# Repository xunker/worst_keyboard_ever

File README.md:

# Worst. Keyboard. Ever.

https://github.com/xunker/worst_keyboard_ever

It's a mechanical keyboard made from limit switches[^1]. Sorry.

## Parts

Part                      | Quantity | Notes
--------------------------|----------|------
[PCB](kicad)              | 1        | Using more than one is not recommended
Omron D2F-FL              | 66       | [^2]
1N4148 Diode              | 66       | SOT-123 package recommended, but you can use LL34 (MiniMELF) if you like things that roll away while you're soldering them
2.54MM pin (male) headers | 23 pos   | Use whatever fits in the holes[^3]
0805 LED                  | 3        | Prefer the kind that light up; LEDs that don't light up are not good indicators
0805 330 ohm resistor     | 3        | You'll learn to solder SMD components and you'll _like it_

Your microcontroller is not listed. Use whatever you like. There's [QMK firmware](#firmware) for the Pi Pico if you want it.

## Matrix

| row/col | 0    | 1   | 2   | 3    | 4    | 5    | 6    | 7   | 8   | 9   | 10  | 11   | 12   | 13    |
|---------|------|-----|-----|------|------|------|------|-----|-----|-----|-----|------|------|-------|
| 0       | esc  | 1   | 2   | 3    | 4    | 5    | 6    | 7   | 8   | 9   | 0   | -    | =    | bksp  |
| 1       | tab  | q   | w   | e    | r    | t    | y    | u   | i   | o   | p   | [    | ]    | \     |
| 2       | cap  | a   | s   | d    | f    | g    | h    | j   | k   | l   | ;   | '    | ent  | ---   |
| 3       | shft | z   | x   | c    | v    | b    | n    | m   | ,   | .   | /   | shft | up   | fn    |
| 4       | ctrl | win | alt |  --- | spc1 | spc2 | spc3 | --- | --- | alt | app | left | down | right |

## LEDs

The caps/num/scroll LEDs are _active-low_. That means the `common` pin should be connected to your microcontroller's VCC, and the LEDs are activated by pulling the approriate pin to ground.

If you're using a 3.3V MCU like the Pi Pico, do **NOT** connect `common` to a 5V source like VBUS or USB power. If you do that, you'll _fry_ your MCU you'll be sad.

## Firmware

There is QMK firmware available, targeting the Raspberry Pi Pico (RP2040). Find it in the [qmk_firmware](qmk_firmware/keyboards/wke_66) directory.

If you don't want to build it yourself, and you don't need to customize anything, a [prebuild .u2f file](./wke_wke_66_default.uf2) is also available.

# Useless Questions

## Why?

Because I needed **one** switch, but it was cheaper to buy a whole gross of them.

## The switches are too close together

I recommend installing smaller fingers on one or both hands.

## I've used worse keyboards than this!

1) "Worst. Keyboard. Ever." is a product/marketing name.
2) No you haven't.

## A Scroll Lock LED? Really?

Don't worry about it. No one in the history of the world has **ever** used Scroll Lock. No, not even _that one guy from the internet_, he's lying.

## Is there an ISO version?

Assuming drills exist, yes.

## It has no legends!

If you're asking for key legends, that means you want to use this as an _actual_ keyboard to type _real_ things. That's a crazy idea, you should stand up and slowly back away.

But, if you insist, [here are some suggestions](SERIOUSLY.md#no-legends).

## Your soldering is terrible!

Wrong, _MY_ soldering is AWESOME. My _cat's_ soldering is terrible.

Note: Cat hair seen in the [photos](images/) is __not included__.

# License

[CC BY-NC-SA 4.0](LICENSE)

[^1]: Variously called "limit switches", "lever switches", or "detect switches".

[^2]: Be honest, you're not going to use _real_ Omron switches, are you? You're going to use some knock-off, admit it.

[^3]: That's what she said.

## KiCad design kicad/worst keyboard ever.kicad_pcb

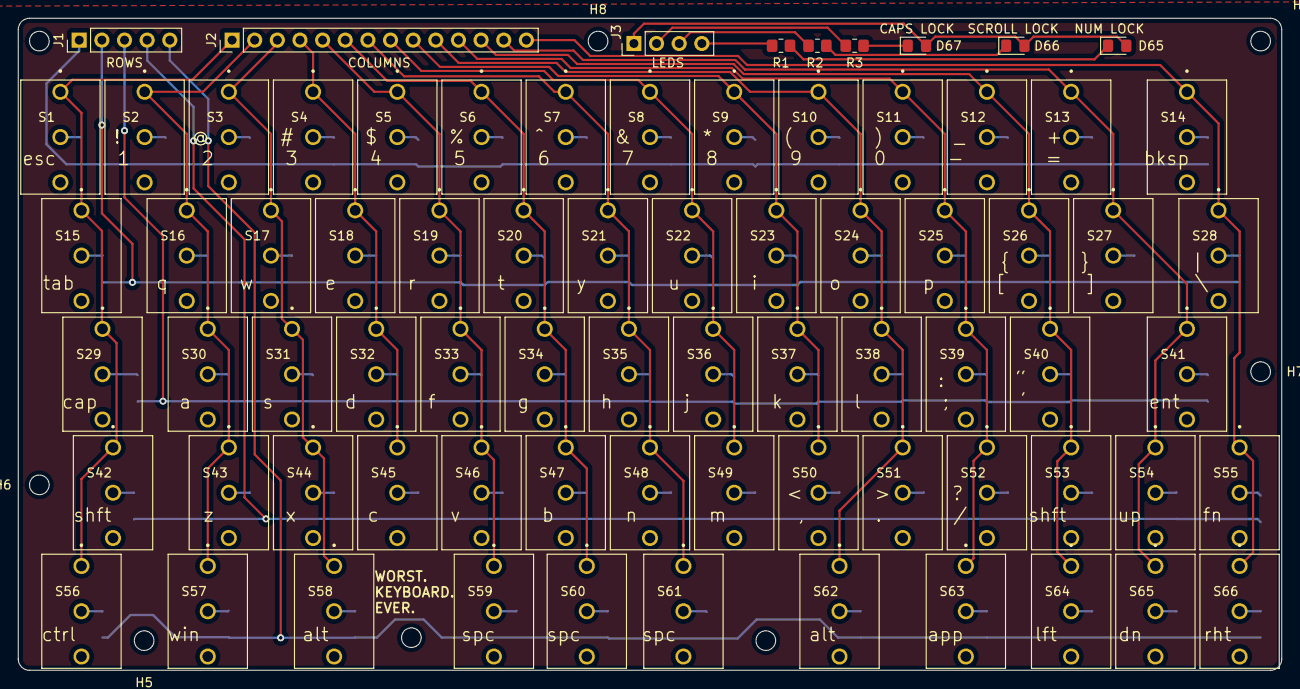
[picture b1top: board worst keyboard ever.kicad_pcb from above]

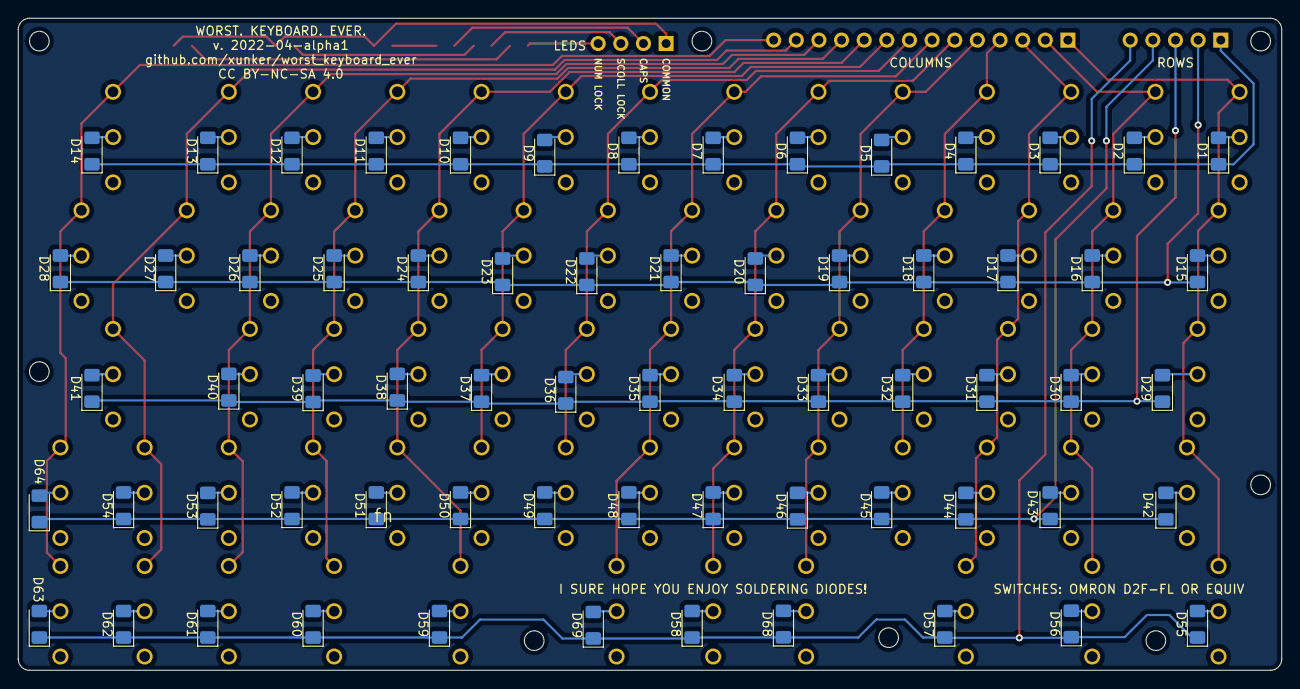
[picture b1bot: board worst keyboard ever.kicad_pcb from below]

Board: 2 copper layers, 141.8 x 73.1 mm, 149 parts (66 on the bottom side), 92 nets.

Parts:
D1, D2, D3, D4, D5, D6, D7, D8, D9, D10, D11, D12, D13, D14, D15, D16, D17, D18, D19, D20, D21, D22, D23, D24, D25, D26, D27, D28, D29, D30, D31, D32, D33, D34, D35, D36, D37, D38, D39, D40, D41, D42, D43, D44, D45, D46, D47, D48, D49, D50, D51, D52, D53, D54, D55, D56, D57, D58, D59, D60, D61, D62, D63, D64, D68, D69: D; D_1206_3216Metric_Pad1.42x1.75mm_HandSolder
D65, D66, D67: LED; LED_0805_2012Metric_Pad1.15x1.40mm_HandSolder
H1, H2, H3, H4, H5, H6, H7, H8: MountingHole; MountingHole_2.2mm_M2_DIN965
J1: Conn_01x05_Male; PinHeader_1x05_P2.54mm_Vertical
J2: Conn_01x14_Male; PinHeader_1x14_P2.54mm_Vertical
J3: Conn_01x04_Male; PinHeader_1x04_P2.54mm_Vertical
R1, R2, R3: R; R_0805_2012Metric_Pad1.20x1.40mm_HandSolder
S1, S2, S3, S4, S5, S6, S7, S8, S9, S10, S11, S12, S13, S14, S15, S16, S17, S18, S19, S20, S21, S22, S23, S24, S25, S26, S27, S28, S29, S30, S31, S32, S33, S34, S35, S36, S37, S38, S39, S40, S41, S42, S43, S44, S45, S46, S47, S48, S49, S50, S51, S52, S53, S54, S55, S56, S57, S58, S59, S60, S61, S62, S63, S64, S65, S66: D2F-FL; SW_D2F-FL_rotated_1.5xwide

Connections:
/CAPS_LOCK_LED: J3.2, R3.2
/LED_COMMON: D65.2 (A), D66.2 (A), D67.2 (A), J3.1
/NUM_LOCK_LED: J3.4, R1.2
/Row1: D1.1 (K), D2.1 (K), D3.1 (K), D4.1 (K), D5.1 (K), D6.1 (K), D7.1 (K), D8.1 (K), D9.1 (K), D10.1 (K), D11.1 (K), D12.1 (K), D13.1 (K), D14.1 (K), J1.1
/Row2: D15.1 (K), D16.1 (K), D17.1 (K), D18.1 (K), D19.1 (K), D20.1 (K), D21.1 (K), D22.1 (K), D23.1 (K), D24.1 (K), D25.1 (K), D26.1 (K), D27.1 (K), D28.1 (K), J1.2
/Row3: D29.1 (K), D30.1 (K), D31.1 (K), D32.1 (K), D33.1 (K), D34.1 (K), D35.1 (K), D36.1 (K), D37.1 (K), D38.1 (K), D39.1 (K), D40.1 (K), D41.1 (K), J1.3
/Row4: D42.1 (K), D43.1 (K), D44.1 (K), D45.1 (K), D46.1 (K), D47.1 (K), D48.1 (K), D49.1 (K), D50.1 (K), D51.1 (K), D52.1 (K), D53.1 (K), D54.1 (K), D64.1 (K), J1.4
/Row5: D55.1 (K), D56.1 (K), D57.1 (K), D58.1 (K), D59.1 (K), D60.1 (K), D61.1 (K), D62.1 (K), D63.1 (K), D68.1 (K), D69.1 (K), J1.5
/SCROLL_LOCK_LED: J3.3, R2.2
Col1: J2.1, S1.COM, S15.COM, S29.COM, S42.COM, S56.COM
Col2: J2.2, S2.COM, S16.COM, S30.COM, S43.COM, S57.COM
Col3: J2.3, S3.COM, S17.COM, S31.COM, S44.COM, S58.COM
Col4: J2.4, S4.COM, S18.COM, S32.COM, S45.COM
Col5: J2.5, S5.COM, S19.COM, S33.COM, S46.COM, S59.COM
Col6: J2.6, S6.COM, S20.COM, S34.COM, S47.COM, S60.COM
Col7: J2.7, S7.COM, S21.COM, S35.COM, S48.COM, S61.COM
Col8: J2.8, S8.COM, S22.COM, S36.COM, S49.COM
Col9: J2.9, S9.COM, S23.COM, S37.COM, S50.COM
Col10: J2.10, S10.COM, S24.COM, S38.COM, S51.COM, S62.COM
Col11: J2.11, S11.COM, S25.COM, S39.COM, S52.COM, S63.COM
Col12: J2.12, S12.COM, S26.COM, S40.COM, S53.COM, S64.COM
Col13: J2.13, S13.COM, S27.COM, S41.COM, S54.COM, S65.COM
Col14: J2.14, S14.COM, S28.COM, S55.COM, S66.COM
unnamed: D1.2 (A), S1.NO
unnamed: D2.2 (A), S2.NO
unnamed: D3.2 (A), S3.NO
unnamed: D4.2 (A), S4.NO
unnamed: D5.2 (A), S5.NO
unnamed: D6.2 (A), S6.NO
unnamed: D7.2 (A), S7.NO
unnamed: D8.2 (A), S8.NO
unnamed: D9.2 (A), S9.NO
unnamed: D10.2 (A), S10.NO
unnamed: D11.2 (A), S11.NO
unnamed: D12.2 (A), S12.NO
unnamed: D13.2 (A), S13.NO
unnamed: D14.2 (A), S14.NO
unnamed: D15.2 (A), S15.NO
unnamed: D16.2 (A), S16.NO
unnamed: D17.2 (A), S17.NO
unnamed: D18.2 (A), S18.NO
unnamed: D19.2 (A), S19.NO
unnamed: D20.2 (A), S20.NO
unnamed: D21.2 (A), S21.NO
unnamed: D22.2 (A), S22.NO
unnamed: D23.2 (A), S23.NO
unnamed: D24.2 (A), S24.NO
unnamed: D25.2 (A), S25.NO
unnamed: D26.2 (A), S26.NO
unnamed: D27.2 (A), S27.NO
unnamed: D28.2 (A), S28.NO
unnamed: D29.2 (A), S29.NO
unnamed: D30.2 (A), S30.NO
unnamed: D31.2 (A), S31.NO
unnamed: D32.2 (A), S32.NO
unnamed: D33.2 (A), S33.NO
unnamed: D34.2 (A), S34.NO
unnamed: D35.2 (A), S35.NO
unnamed: D36.2 (A), S36.NO
unnamed: D37.2 (A), S37.NO
unnamed: D38.2 (A), S38.NO
unnamed: D39.2 (A), S39.NO
unnamed: D40.2 (A), S40.NO
unnamed: D41.2 (A), S41.NO
unnamed: D42.2 (A), S42.NO
unnamed: D43.2 (A), S43.NO
unnamed: D44.2 (A), S44.NO
unnamed: D45.2 (A), S45.NO
unnamed: D46.2 (A), S46.NO
unnamed: D47.2 (A), S47.NO
unnamed: D48.2 (A), S48.NO
unnamed: D49.2 (A), S49.NO
unnamed: D50.2 (A), S50.NO
unnamed: D51.2 (A), S51.NO
unnamed: D52.2 (A), S52.NO
unnamed: D53.2 (A), S53.NO
unnamed: D54.2 (A), S54.NO
unnamed: D55.2 (A), S56.NO
unnamed: D56.2 (A), S57.NO
unnamed: D57.2 (A), S58.NO
unnamed: D58.2 (A), S60.NO
unnamed: D59.2 (A), S62.NO
unnamed: D60.2 (A), S63.NO
unnamed: D61.2 (A), S64.NO
unnamed: D62.2 (A), S65.NO
unnamed: D63.2 (A), S66.NO
unnamed: D64.2 (A), S55.NO
unnamed: D65.1 (K), R1.1
unnamed: D66.1 (K), R2.1
unnamed: D67.1 (K), R3.1
unnamed: D68.2 (A), S59.NO
unnamed: D69.2 (A), S61.NO

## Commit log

2026-05-05 initial commit, only took 4 years
2026-05-06 drill > scissors
2026-05-06 Seriously.
2026-05-06 move legend suggestions
2026-05-06 Add LED info and voltage warning
2026-05-06 Add prebuilt firmware file
